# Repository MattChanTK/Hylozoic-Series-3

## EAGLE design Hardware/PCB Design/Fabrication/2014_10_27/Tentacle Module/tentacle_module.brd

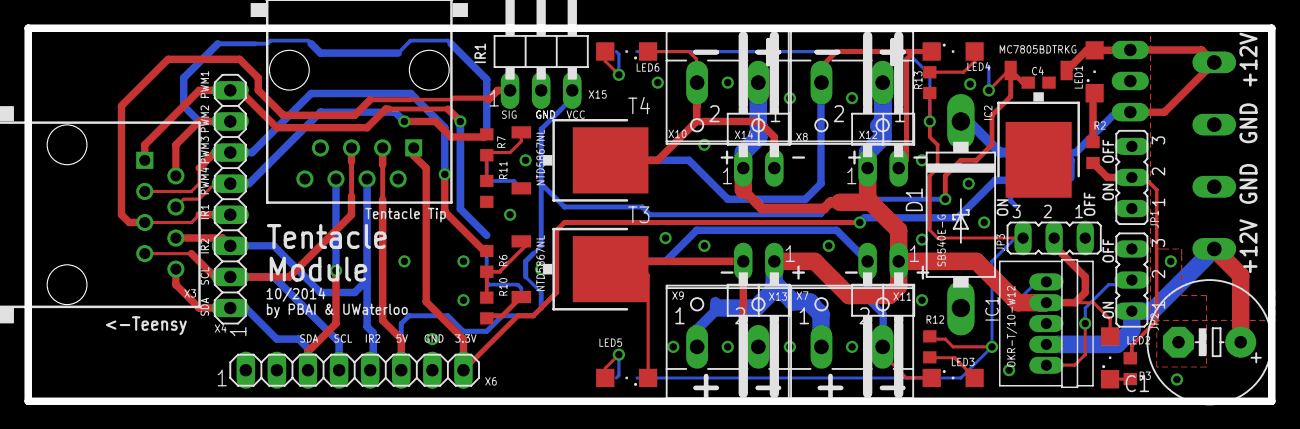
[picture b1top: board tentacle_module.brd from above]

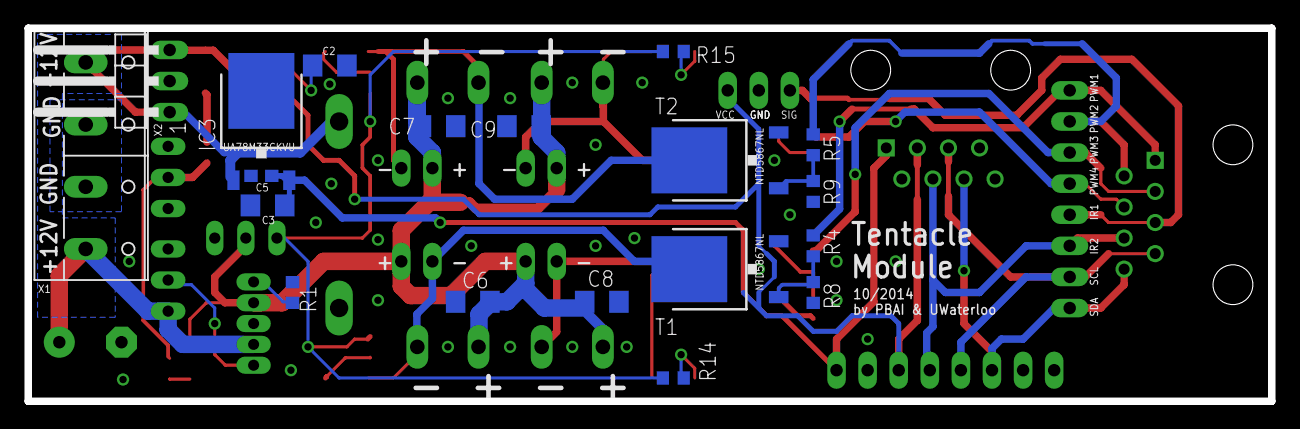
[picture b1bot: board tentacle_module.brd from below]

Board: 2 copper layers, 101.6 x 30.5 mm, 56 parts (19 on the bottom side), 31 nets.

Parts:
C1: 470uF; E5-10,5
C2, C3, C6, C7, C8, C9: 10uF; C1206
C4, C5: 100nF; C0603
D1: SB540E-G; DO201T15
IC1: OKR-T/10-W12; OKR-C90
IC2: MC7805BDTRKG; DPACK_3
IC3: UA78M33CKVU; DPACK
JP1, JP2, JP3: JP2
LED1, LED2, LED3, LED4, LED5, LED6: SML1206
R1: 267; R0603
R2, R3, R12, R13, R14, R15: 470; R0603
R4, R5, R6, R7: 1K; R0603
R8, R9, R10, R11: 4.7K; R0603
T1, T2, T3, T4: NTD5867NL; DPACK
X1: W237-4P
X2, X15: 1X03/90
X3, X5: RJ45-8X; RJ45-NO-SHIELD
X4, X6: 1X08
X7, X8, X9, X10: W237-102
X11, X12, X13, X14: 1X02/90

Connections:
5V_ENABLE: IC1.ON/OFF, JP2.2
+3.3V: C3.1, C5.1, IC3.3, X5.1, X6.8
+5V: C2.1, C4.1, IC2.3, X5.3, X6.6, X15.3
+5V_HI-PWR: C6.1, C7.1, C8.1, C9.1, IC1.VOUT, JP3.2, LED2.A, X7.1, X8.1, X9.1, X10.1, X11.1, X12.1, X13.1, X14.1
+12V: C1.+, D1.C, IC1.VIN, IC2.1, IC3.1, JP2.1, LED1.A, X1.1, X1.4, X2.1, X2.3
GND: C1.-, C2.2, C3.2, C4.2, C5.2, C6.2, C7.2, C8.2, C9.2, D1.A, IC1.GND, IC2.4, IC3.2, JP1.1, JP2.3, R1.1, R8.1, R9.1, R10.1, R11.1, T1.3, T2.3, T3.3, T4.3, X1.2, X1.3, X2.2, X5.2, X6.7, X15.2
IR1: X3.5, X4.4, X15.1
IR2: X3.6, X4.3, X5.4, X6.5
unnamed: R5.2, R9.2, T2.1
unnamed: R6.2, R10.2, T3.1
unnamed: R7.2, R11.2, T4.1
unnamed: R4.2, R8.2, T1.1
unnamed: LED3.A, R12.1
unnamed: IC1.TRIM, R1.2
unnamed: LED2.C, R3.2
unnamed: LED1.C, R2.2
unnamed: LED4.A, R13.1
unnamed: LED5.A, R14.1
unnamed: LED6.A, R15.1
PWM1: R4.1, X3.1, X4.8
PWM2: R5.1, X3.2, X4.7
PWM3: R6.1, X3.3, X4.6
PWM4: R7.1, X3.4, X4.5
PWR_LED_GND: JP1.2, R2.1, R3.1
SCL: X3.7, X4.2, X5.5, X6.4
SDA: X3.8, X4.1, X5.6, X6.3
SMA1_OUT-: LED3.C, T1.2, X7.2, X11.2
SMA2_OUT-: LED4.C, T2.2, X8.2, X12.2
SMA3_OUT-: LED5.C, T3.2, X9.2, X13.2
SMA4_OUT-: LED6.C, T4.2, X10.2, X14.2
TEST_LED_V+: JP3.3, R12.2, R13.2, R14.2, R15.2

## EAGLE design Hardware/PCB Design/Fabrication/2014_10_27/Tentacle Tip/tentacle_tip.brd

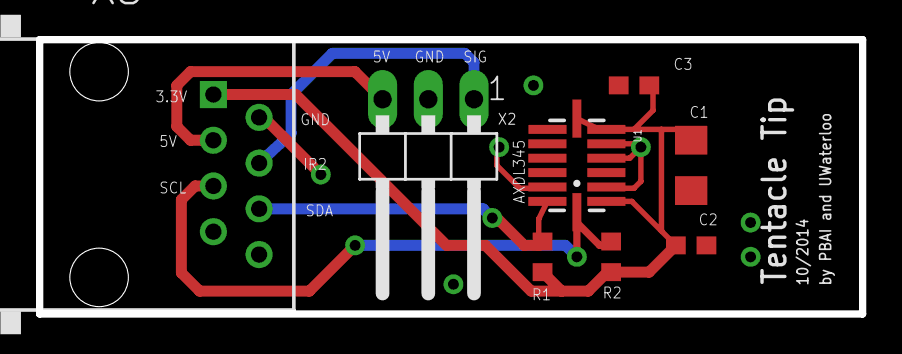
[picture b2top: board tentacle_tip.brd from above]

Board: 2 copper layers, 45.7 x 15.2 mm, 8 parts (0 on the bottom side), 6 nets.

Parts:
C1: 10uF; C1206
C2, C3: 0.1uF; C0603
R1, R2: 2.2k; R0603
U1: ADXL345; LGA14_LONG
X2: 1X03/90
X3: RJ45-8X; RJ45-NO-SHIELD

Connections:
+3.3V: C1.1, C2.1, C3.1, R1.2, R2.2, U1.1, U1.6, U1.7, X3.1
+5V: X2.3, X3.3
GND: C1.2, C2.2, C3.2, U1.2, U1.4, U1.5, U1.12, X2.2, X3.2
IR2: X2.1, X3.4
SCL: R2.1, U1.14, X3.5
SDA: R1.1, U1.13, X3.6

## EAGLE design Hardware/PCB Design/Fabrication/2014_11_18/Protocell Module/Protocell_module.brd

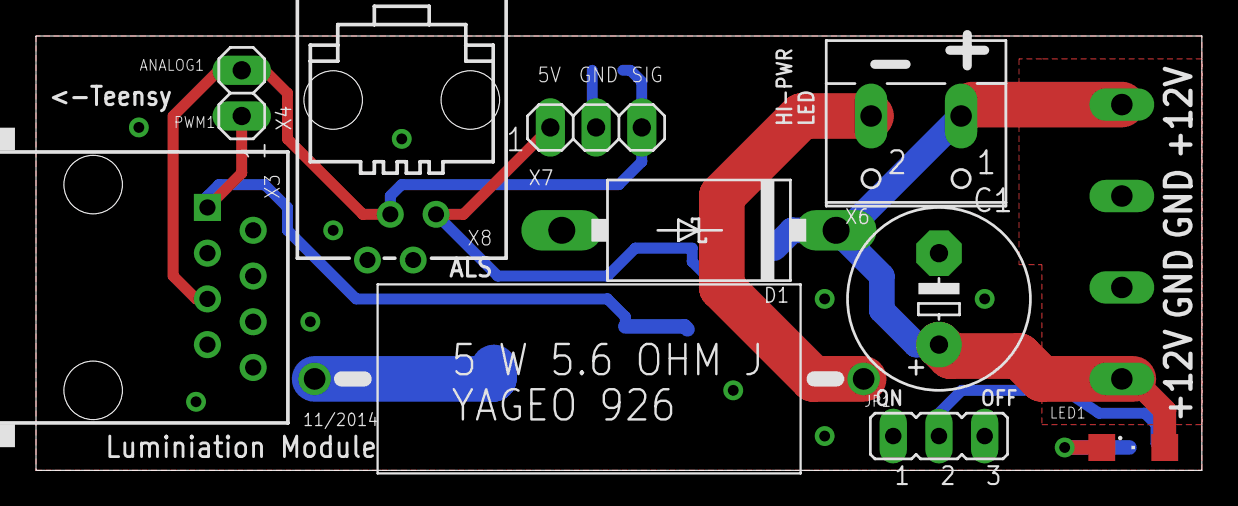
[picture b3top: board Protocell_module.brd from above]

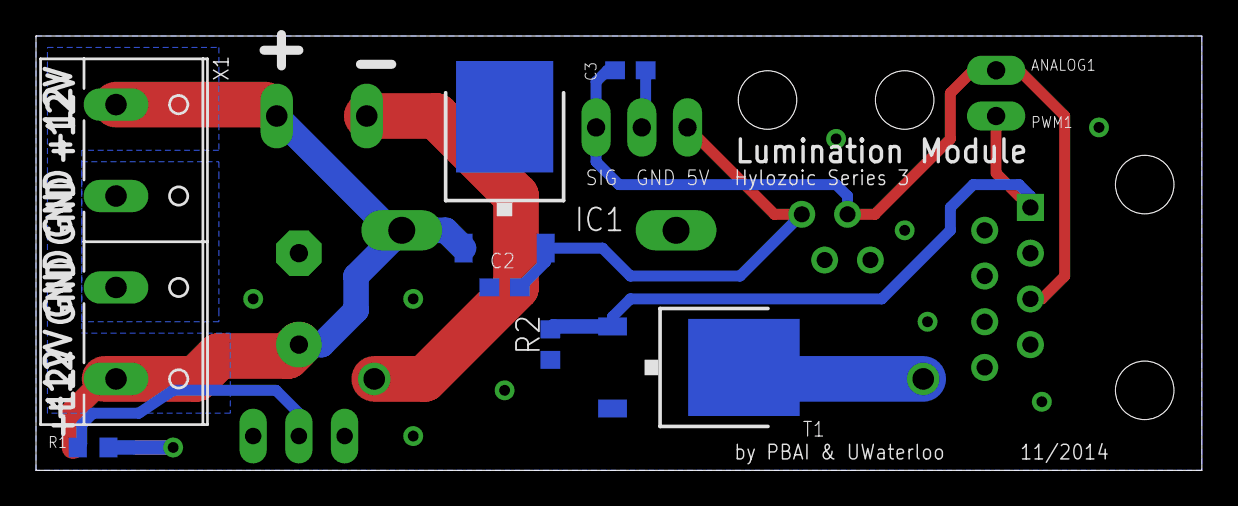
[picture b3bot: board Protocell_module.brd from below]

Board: 2 copper layers, 64.8 x 24.1 mm, 17 parts (7 on the bottom side), 9 nets.

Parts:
C1: 470uF; E5-10,5
C2, C3: 1uF; C0603
D1: SB540E-G; DO201T15
IC1: MC7805BDTRKG; DPACK_3
JP1: JP2
LED1: SML1206
R1: 470; R0603
R2: 4.7k; R0603
R3: 5.6; YAGEO_SQP500JB
T1: DPACK
X1: W237-4P
X3: RJ45-8X; RJ45-NO-SHIELD
X4: 1X02
X6: W237-102
X7: 1X03
X8: 558872-1

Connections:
+5V: C2.1, IC1.3, X7.1, X8.1
+12V: C1.+, D1.C, IC1.1, LED1.A, X1.1, X1.4, X6.1
ANALOG1: C3.1, X3.5, X4.2, X7.3, X8.3
GND: C1.-, C2.2, C3.2, D1.A, IC1.4, JP1.1, R2.1, T1.3, X1.2, X1.3, X7.2, X8.2
unnamed: R3.1, T1.2
unnamed: R3.2, X6.2
unnamed: LED1.C, R1.2
PWM1: R2.2, T1.1, X3.1, X4.1
PWR_LED_GND: JP1.2, R1.1

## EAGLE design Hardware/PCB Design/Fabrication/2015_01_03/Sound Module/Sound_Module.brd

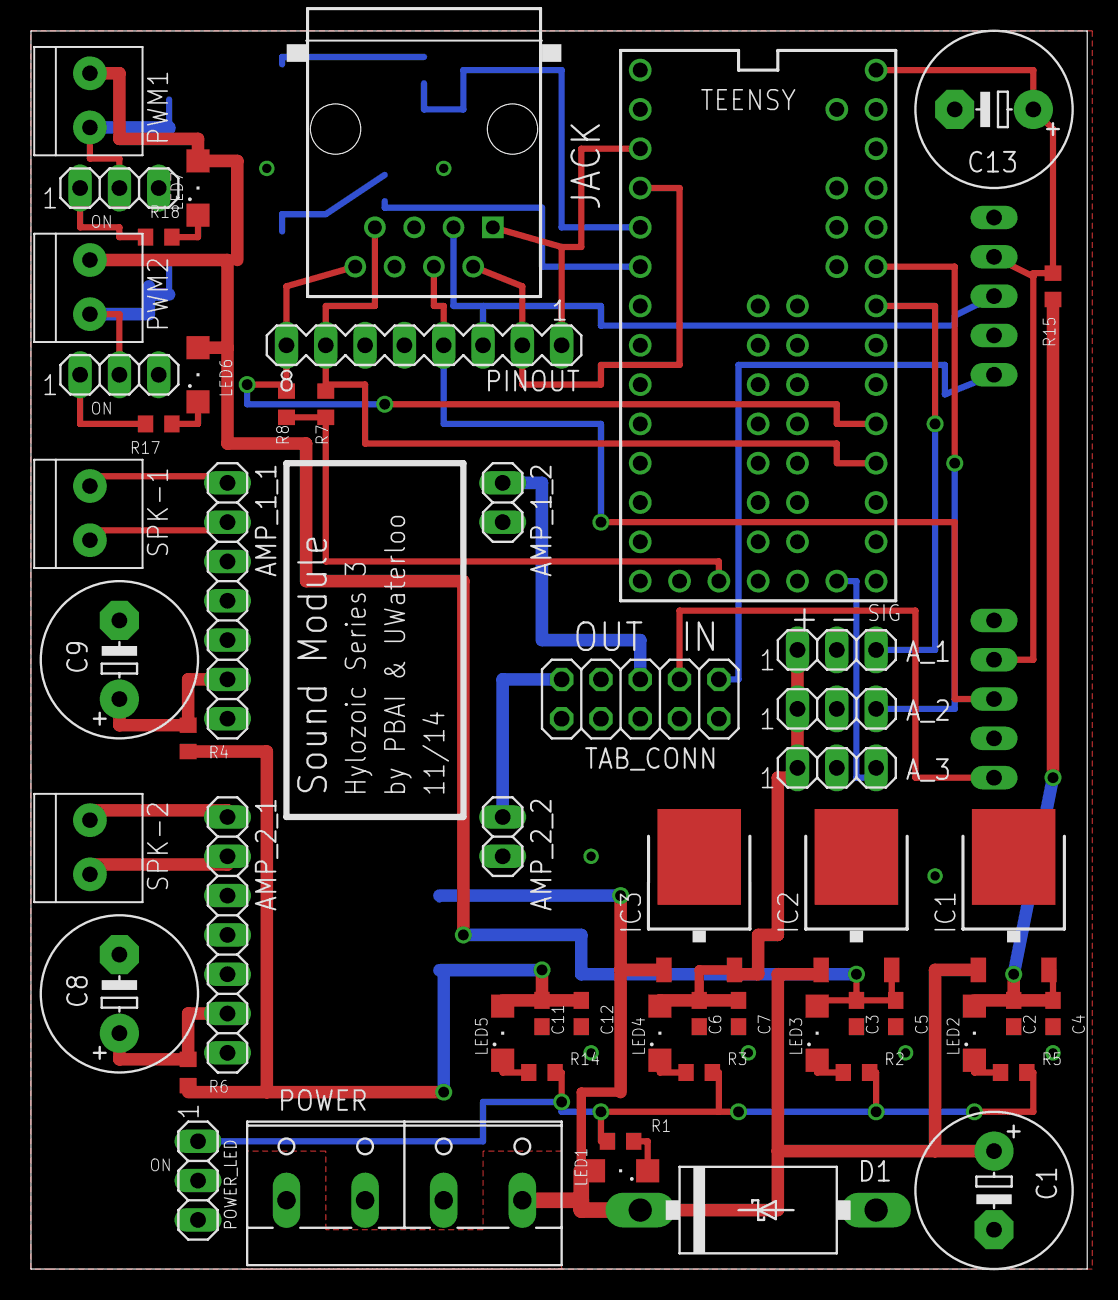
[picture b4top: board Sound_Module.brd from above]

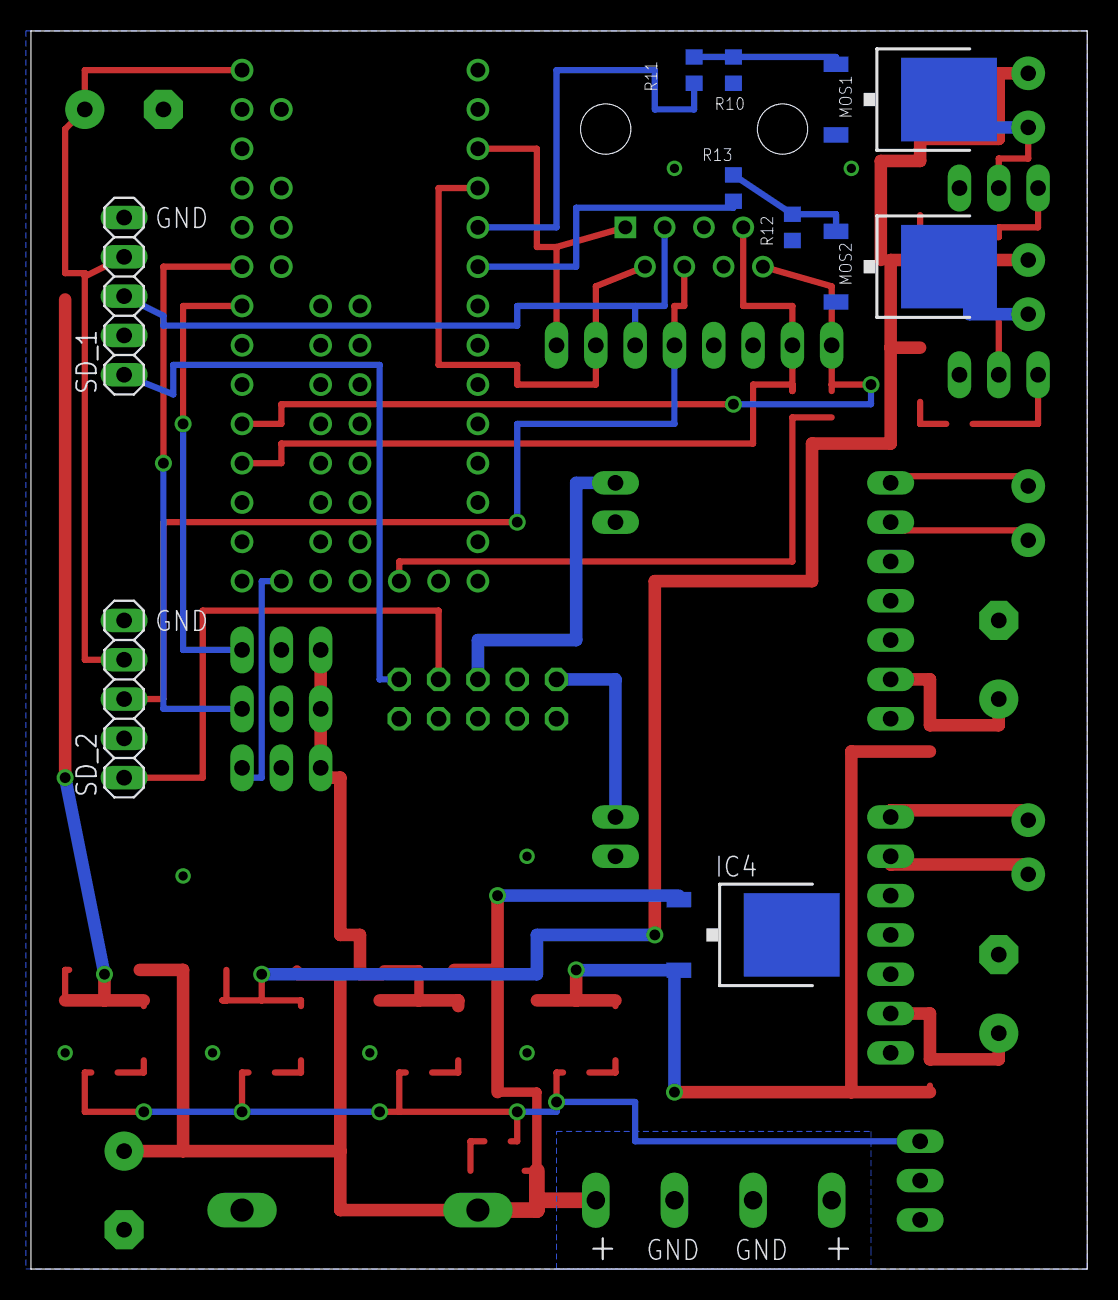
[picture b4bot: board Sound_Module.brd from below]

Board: 2 copper layers, 68.2 x 80.0 mm, 63 parts (9 on the bottom side), 43 nets.

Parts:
AMP_1_1, AMP_2_1: 1X07
AMP_1_2, AMP_2_2: 1X02
A_1, A_2, A_3: 1X03
C1: 2000uF; E5-10,5
C2, C3, C6, C11: 1uF; C0603
C4, C5, C7, C12: 100nF; C0603
C8, C9, C13: 470uF; E5-10,5
D1: SB540E-G; DO201T15
IC1, IC2, IC3, IC4: DPACK_3
JACK: RJ45-6L-B; RJ45-NO-SHIELD
LED1, LED2, LED3, LED4, LED5, LED6, LED7: SML1206
MOS1, MOS2: DPACK
PINOUT: MA08-1
POWER: W237-4P
POWER_LED: 1X03
PWM1, PWM2: 1X2-3.5MM
R1, R2, R3, R5, R14, R17, R18: 470; R0603
R4, R6, R15: 10; R0603
R7, R8: 2.2k; R0603
R10, R12: 4.7K; R0603
R11, R13: 1K; R0603
SD_1, SD_2: 1X05
SPK-1, SPK-2: 1X2-3.5MM
TAB_CONN: 2X05
TEENSY: AUDIO BOARD; TEENSY_3.1_ALLPINS
X2, X3: 1X03

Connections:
3.3V: R7.2, R8.2, TEENSY.3.3V, TEENSY.3.3V1, TEENSY.3.3V2
5VFILT: C13.+, R15.1, SD_1.4, SD_2.4, TEENSY.VIN
+5V_1: C2.1, C4.1, IC1.3, LED2.A, R15.2
+5V_2: C3.1, C5.1, IC2.3, LED3.A, LED6.A, LED7.A, PWM1.2, PWM2.2
+5V_3: A_1.1, A_2.1, A_3.1, C6.1, C7.1, IC3.3, LED4.A
+5V_4: C11.1, C12.1, IC4.3, LED5.A, R4.2, R6.2
+12V: C1.+, D1.C, IC1.1, IC2.1, IC3.1, IC4.1, LED1.A, POWER.1, POWER.4
AMP_1_VIN: AMP_1_1.6, C9.+, R4.1
AMP_2_VIN: AMP_2_1.6, C8.+, R6.1
DPEAK_1: JACK.3, PINOUT.3, SD_1.3
DPEAK_2: JACK.4, PINOUT.4, SD_2.3
DTRIG_1: JACK.1, PINOUT.1, TEENSY.1
DTRIG_2: JACK.2, PINOUT.2, TEENSY.2
FPWM_1_1: R11.2, TEENSY.3
FPWM_1_2: R13.2, TEENSY.4
GND: AMP_1_1.5, AMP_1_2.2, AMP_2_1.5, AMP_2_2.2, A_1.2, A_2.2, A_3.2, C1.-, C2.2, C3.2, C4.2, C5.2, C6.2, C7.2, C8.-, C9.-, C11.2, C12.2, C13.-, D1.A, IC1.4, IC2.4, IC3.4, IC4.4, MOS1.3, MOS2.3, POWER.2, POWER.3, POWER_LED.2, R10.1, R12.1, SD_1.5, SD_2.5, TAB_CONN.2, TAB_CONN.4, TAB_CONN.7, TEENSY.GND, TEENSY.GND1, TEENSY.GND2
IN_1+: AMP_1_2.1, TAB_CONN.5
IN_2+: AMP_2_2.1, TAB_CONN.9
LED_JUMP_POW: POWER_LED.1, R1.1, R2.1, R3.1, R5.1, R14.1
MIC_1: SD_1.1, TAB_CONN.1
MIC_2: SD_2.1, TAB_CONN.3
unnamed: MOS2.1, R12.2, R13.1
unnamed: LED3.C, R2.2
unnamed: LED4.C, R3.2
unnamed: MOS1.1, R10.2, R11.1
unnamed: MOS1.2, PWM1.1, X2.2
unnamed: LED6.C, R17.2
unnamed: MOS2.2, PWM2.1, X3.2
unnamed: LED5.C, R14.2
unnamed: LED7.C, R18.2
unnamed: LED1.C, R1.2
unnamed: R18.1, X2.1
unnamed: R17.1, X3.1
unnamed: LED2.C, R5.2
SCL: JACK.7, PINOUT.7, R7.1, TEENSY.16/A2
SDA: JACK.8, PINOUT.8, R8.1, TEENSY.17/A3
SIG_1: A_1.3, TEENSY.20/A6
SIG_2: A_2.3, TEENSY.21/A7
SIG_3: A_3.3, TEENSY.A14
SPK_1+: AMP_1_1.1, SPK-1.2
SPK_1-: AMP_1_1.2, SPK-1.1
SPK_2+: AMP_2_1.1, SPK-2.2
SPK_2-: AMP_2_1.2, SPK-2.1

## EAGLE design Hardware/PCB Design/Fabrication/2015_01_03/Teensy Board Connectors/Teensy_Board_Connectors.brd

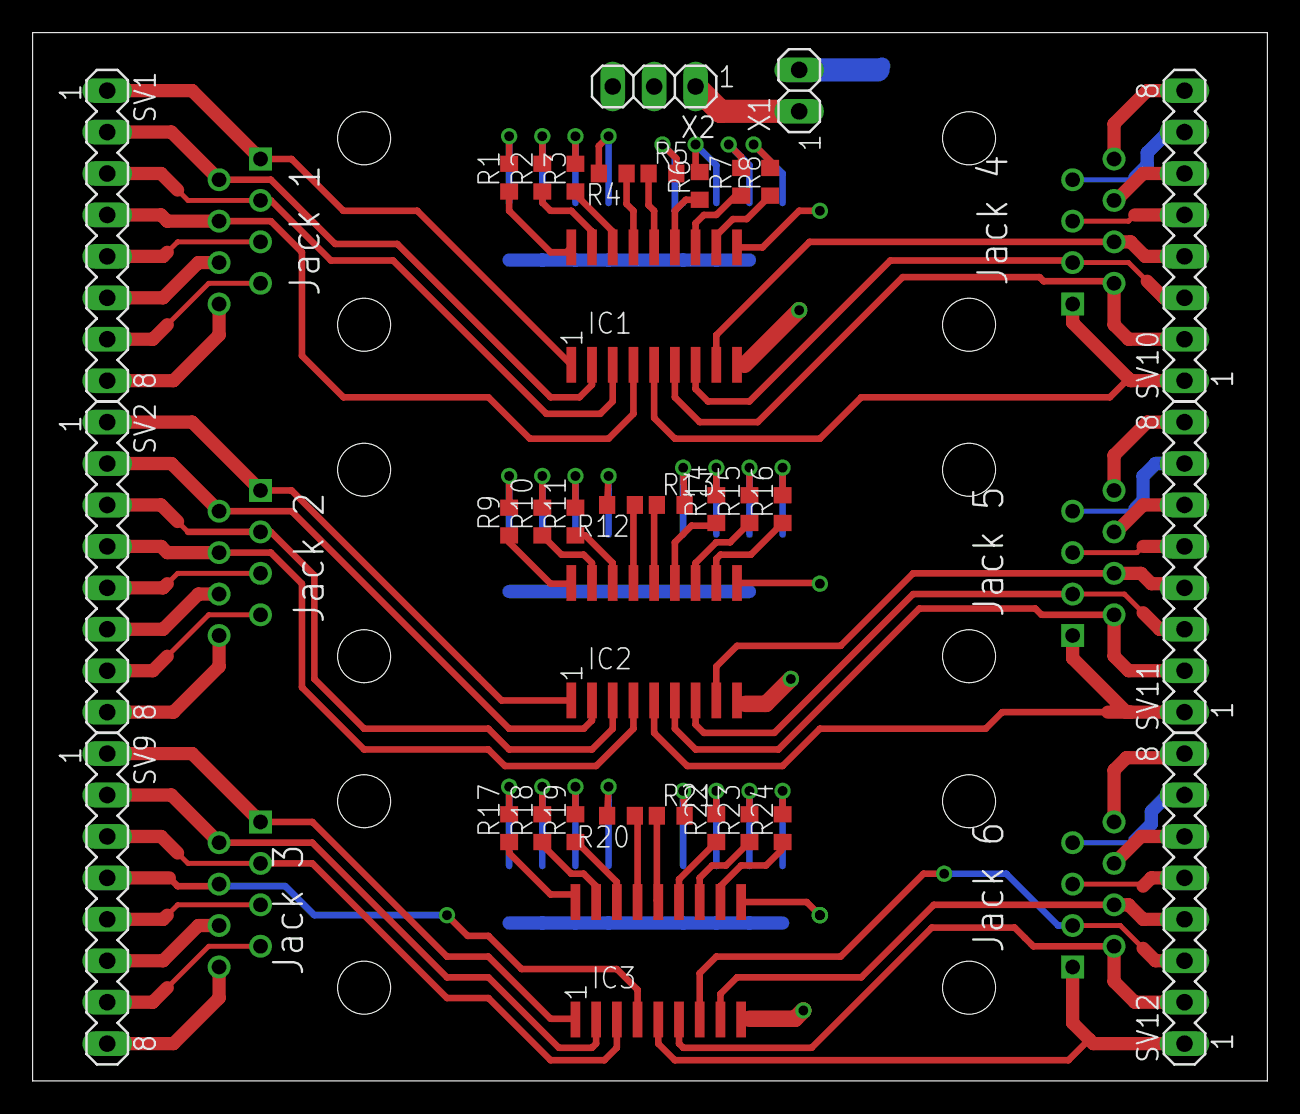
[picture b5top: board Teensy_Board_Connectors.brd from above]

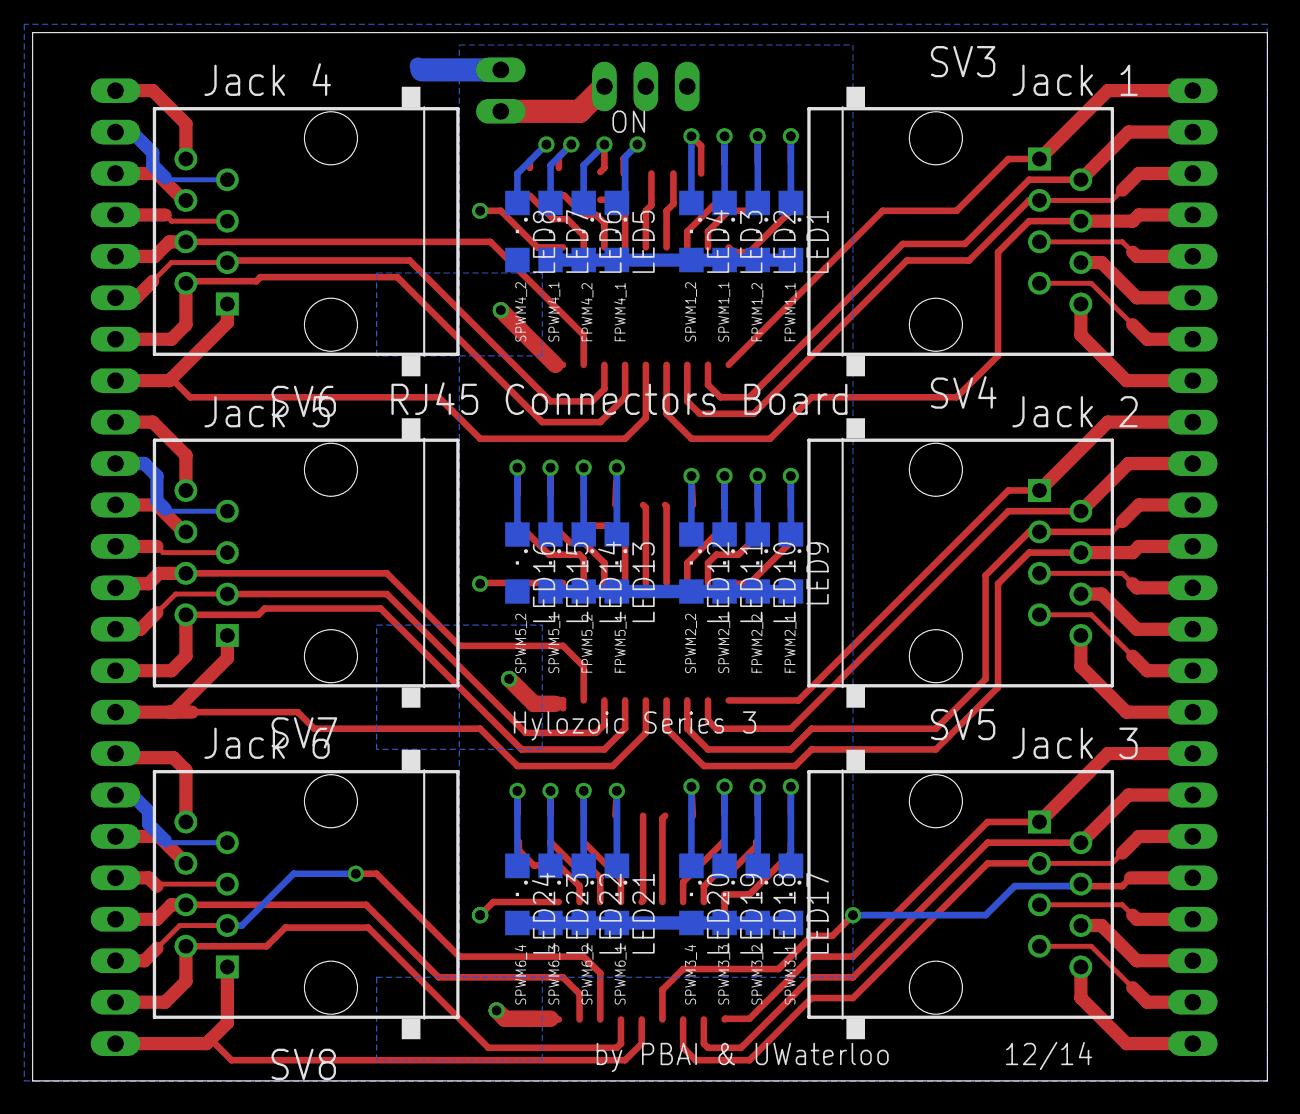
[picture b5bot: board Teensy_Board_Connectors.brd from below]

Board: 2 copper layers, 75.7 x 64.3 mm, 65 parts (30 on the bottom side), 99 nets.

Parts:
IC1, IC2, IC3: SOP18
LED1, LED2, LED3, LED4, LED5, LED6, LED7, LED8, LED9, LED10, LED11, LED12, LED13, LED14, LED15, LED16, LED17, LED18, LED19, LED20, LED21, LED22, LED23, LED24: SML1206
R1, R2, R3, R4, R5, R6, R7, R8, R9, R10, R11, R12, R13, R14, R15, R16, R17, R18, R19, R20, R21, R22, R23, R24: 470; R0603
SV1, SV2, SV9, SV10, SV11, SV12: MA08-1
SV3, SV4, SV5, SV6, SV7, SV8: RJ45-8X; RJ45-NO-SHIELD
X1: 1X02
X2: 1X03

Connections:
+5V: IC1.10, IC2.10, IC3.10, LED1.A, LED2.A, LED3.A, LED4.A, LED5.A, LED6.A, LED7.A, LED8.A, LED9.A, LED10.A, LED11.A, LED12.A, LED13.A, LED14.A, LED15.A, LED16.A, LED17.A, LED18.A, LED19.A, LED20.A, LED21.A, LED22.A, LED23.A, LED24.A, X2.2
+5VJUMP: X1.1, X2.1
A0: SV8.5, SV12.5
A1: SV8.6, SV12.6
A2: SV7.5, SV11.5
A3: SV7.6, SV11.6
A8: SV6.5, SV10.5
A9: SV6.6, SV10.6
A11: SV1.5, SV3.5
A12: SV2.5, SV4.5
A13: SV1.6, SV3.6
A15: SV2.6, SV4.6
A16: SV5.5, SV9.5
A17: SV5.6, SV9.6
FPWM_1_1: IC1.1, SV1.1, SV3.1
FPWM_1_2: IC1.2, SV1.2, SV3.2
FPWM_2_1: IC2.1, SV2.1, SV4.1
FPWM_2_2: IC2.2, SV2.2, SV4.2
FPWM_4_1: IC1.5, SV6.1, SV10.1
FPWM_4_2: IC1.6, SV6.2, SV10.2
FPWM_5_1: IC2.5, SV7.1, SV11.1
FPWM_5_2: IC2.6, SV7.2, SV11.2
GND: IC1.9, IC2.9, IC3.9, X1.2
MUL_SCL_1: SV1.7, SV3.7
MUL_SCL_2: SV2.7, SV4.7
MUL_SCL_3: SV5.7, SV9.7
MUL_SCL_4: SV6.7, SV10.7
MUL_SCL_5: SV7.7, SV11.7
MUL_SCL_6: SV8.7, SV12.7
MUL_SDA_1: SV1.8, SV3.8
MUL_SDA_2: SV2.8, SV4.8
MUL_SDA_3: SV5.8, SV9.8
MUL_SDA_4: SV6.8, SV10.8
MUL_SDA_5: SV7.8, SV11.8
MUL_SDA_6: SV8.8, SV12.8
unnamed: IC1.18, R1.1
unnamed: LED1.C, R1.2
unnamed: IC1.17, R2.1
unnamed: IC1.16, R3.1
unnamed: IC1.15, R4.1
unnamed: IC1.14, R5.1
unnamed: IC1.13, R6.1
unnamed: IC1.12, R7.1
unnamed: IC1.11, R8.1
unnamed: LED2.C, R2.2
unnamed: LED3.C, R3.2
unnamed: LED4.C, R4.2
unnamed: LED5.C, R5.2
unnamed: LED6.C, R6.2
unnamed: LED7.C, R7.2
unnamed: LED8.C, R8.2
unnamed: IC2.18, R9.1
unnamed: LED9.C, R9.2
unnamed: IC2.17, R10.1
unnamed: IC2.16, R11.1
unnamed: IC2.15, R12.1
unnamed: IC2.14, R13.1
unnamed: IC2.13, R14.1
unnamed: IC2.12, R15.1
unnamed: IC2.11, R16.1
unnamed: LED10.C, R10.2
unnamed: LED11.C, R11.2
unnamed: LED12.C, R12.2
unnamed: LED13.C, R13.2
unnamed: LED14.C, R14.2
unnamed: LED15.C, R15.2
unnamed: LED16.C, R16.2
unnamed: IC3.18, R17.1
unnamed: LED17.C, R17.2
unnamed: IC3.17, R18.1
unnamed: IC3.16, R19.1
unnamed: IC3.15, R20.1
unnamed: IC3.14, R21.1
unnamed: IC3.13, R22.1
unnamed: IC3.12, R23.1
unnamed: IC3.11, R24.1
unnamed: LED18.C, R18.2
unnamed: LED19.C, R19.2
unnamed: LED20.C, R20.2
unnamed: LED21.C, R21.2
unnamed: LED22.C, R22.2
unnamed: LED23.C, R23.2
unnamed: LED24.C, R24.2
SPWM_1_1: IC1.3, SV1.3, SV3.3
SPWM_1_2: IC1.4, SV1.4, SV3.4
SPWM_2_1: IC2.3, SV2.3, SV4.3
SPWM_2_2: IC2.4, SV2.4, SV4.4
SPWM_3_1: IC3.1, SV5.1, SV9.1
SPWM_3_2: IC3.2, SV5.2, SV9.2
SPWM_3_3: IC3.3, SV5.3, SV9.3
SPWM_3_4: IC3.4, SV5.4, SV9.4
SPWM_4_1: IC1.7, SV6.3, SV10.3
SPWM_4_2: IC1.8, SV6.4, SV10.4
SPWM_5_1: IC2.7, SV7.3, SV11.3
SPWM_5_2: IC2.8, SV7.4, SV11.4
SPWM_6_1: IC3.5, SV8.1, SV12.1
SPWM_6_2: IC3.6, SV8.2, SV12.2
SPWM_6_3: IC3.7, SV8.3, SV12.3
SPWM_6_4: IC3.8, SV8.4, SV12.4

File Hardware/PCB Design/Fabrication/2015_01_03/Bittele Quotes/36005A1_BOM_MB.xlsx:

| Tentacle Tip Bill of Materials (BOM)_Bittele Electronics Inc.
Item # | Ref Des | Description | Qty | Manufacturer | Mfg Part # | Package | Type | Your Instructions |  | Total Required for 10 Boards | Packed
1 | LED1, LED2, LED3, LED4, LED5, LED6, LED7, LED8, LED9, LED10, LED11, LED12, LED1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 | LED 3.2X1.6MM 568NM GRN CLR SMD | 24 | Kingbright | APTR3216SGC | 1206 | SMD |  |  | 240 | 0
2 | SV1, SV2, SV9, SV10, SV11, SV12 | CONN HEADER .100" SNGL STR 8POS | 6 | Sullins Connector Solutions | PREC008SAAN-RC | 0.100" (2.54mm) | thru-hole |  |  | 60 | 0
3 | X1 | CONN HEADER .100" SNGL STR 2POS | 1 | Sullins Connector Solutions | PREC002SAAN-RC | 0.100" (2.54mm) | thru-hole |  |  | 10 | 0
4 | X2 | CONN HEADER .100" SNGL STR 3POS | 1 | Sullins Connector Solutions | PREC003SAAN-RC | 0.100" (2.54mm) | thru-hole |  |  | 10 | 0
5 | IC1, IC2, IC3 | TRANS 8NPN DARL 50V 0.5A 18SOL | 3 | Toshiba Semiconductor and Storage | ULN2803AFWG,C,EL | 18-SOIC | SMD |  |  | 30 | 0
6 | R1, R2, R3, R4, R5, R6, R7, R8, R9, R10, R11, R12, R13, R14, R15, R16, R17, R18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 | RES 470 OHM 1/4W 5% 0603 SMD | 24 | Rohm Semiconductor | RHM470DCT-ND | 0603 | SMD |  |  | 240 | 0
7 | SV3, SV4, SV5, SV6, SV7, SV8 | CONN MOD JACK 8P8C | 6 | FCI | 54602-908LF |  | thru-hole |  |  | 60 | 63

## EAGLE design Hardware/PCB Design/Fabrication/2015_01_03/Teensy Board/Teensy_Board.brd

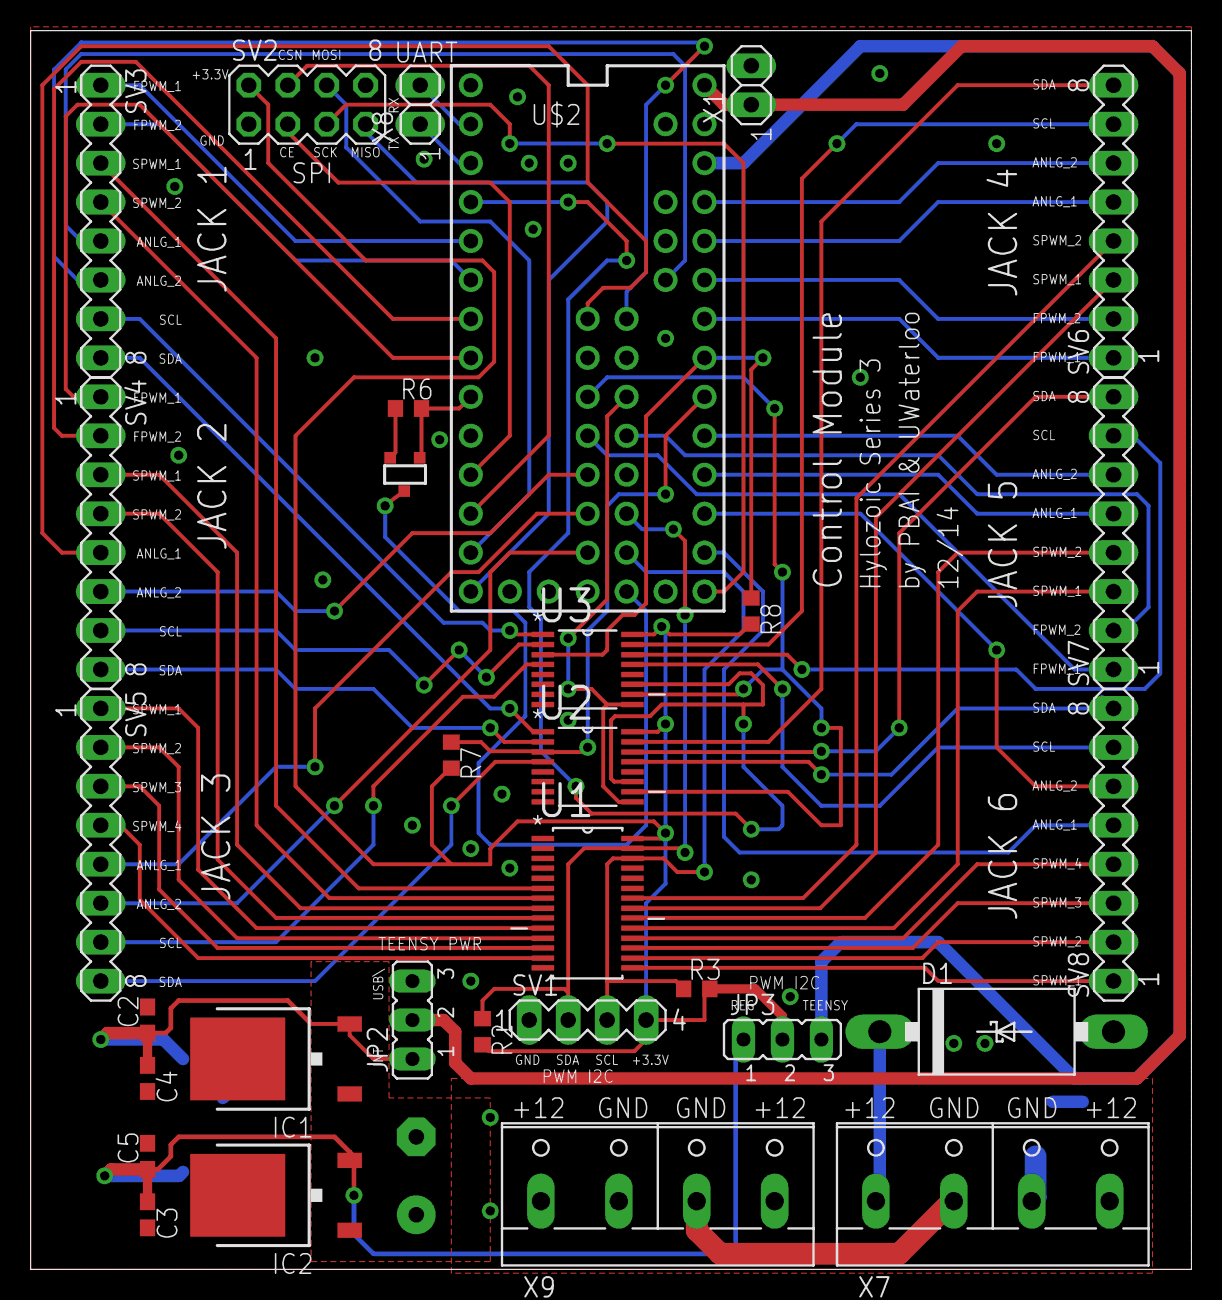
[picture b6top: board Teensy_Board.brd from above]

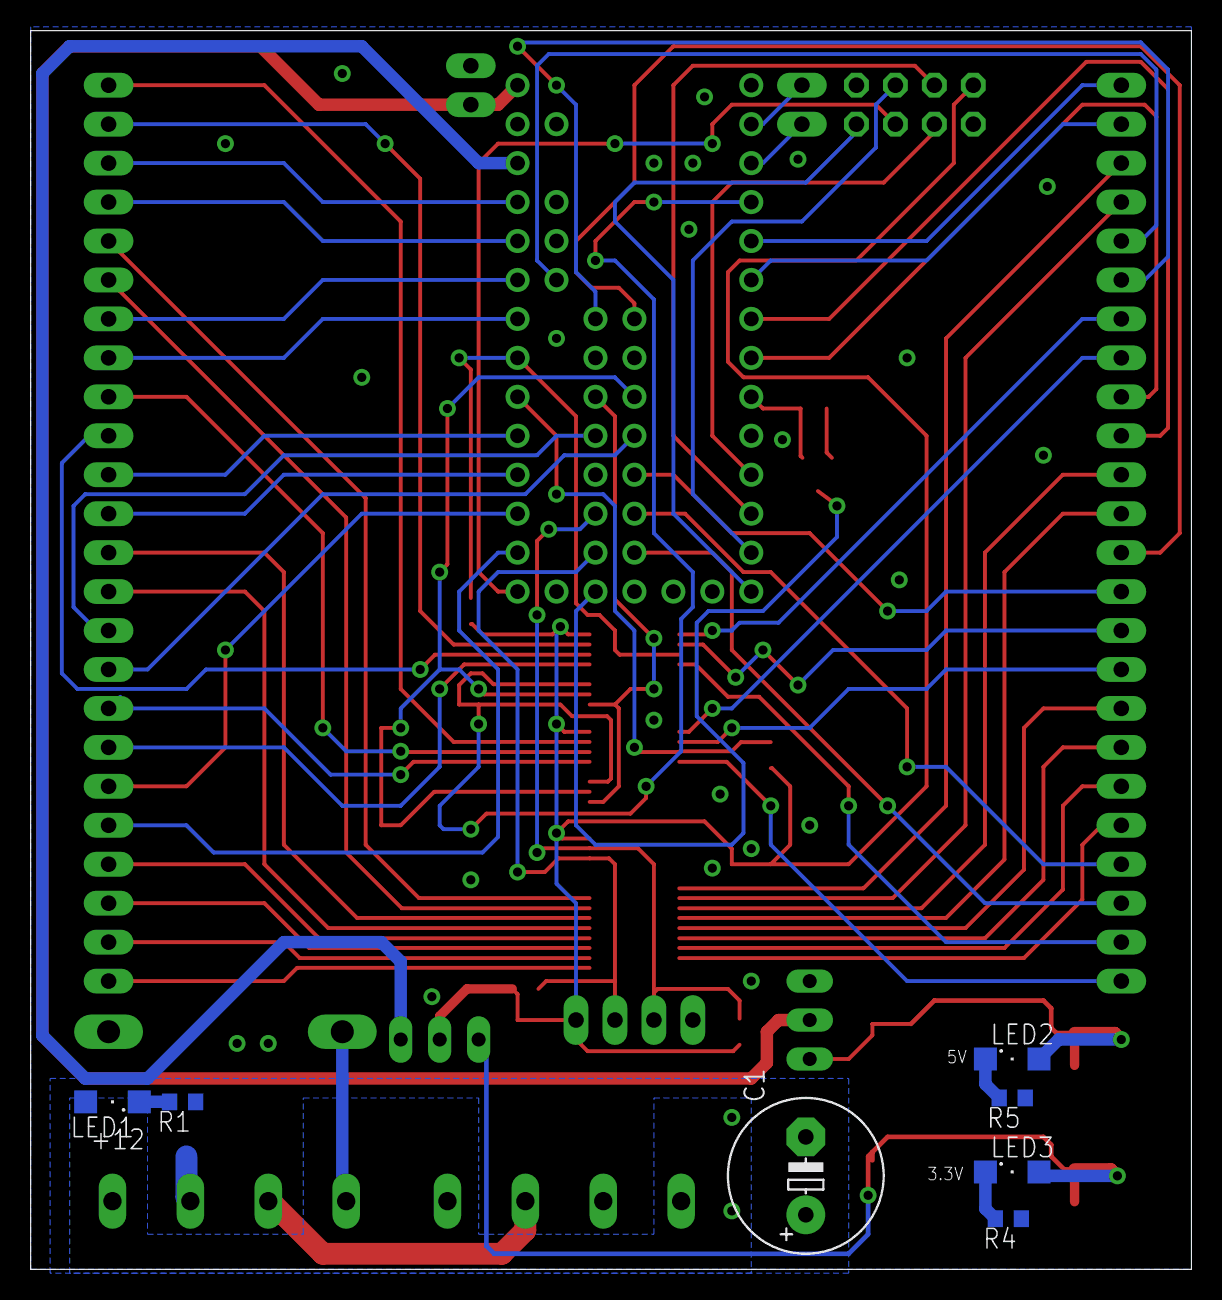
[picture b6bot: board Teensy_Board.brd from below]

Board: 2 copper layers, 75.7 x 80.8 mm, 38 parts (7 on the bottom side), 74 nets.

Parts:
C1: 470uF; E5-10,5
C2, C3: 1uF; C0603
C4, C5: 100nF; C0603
D1: SB540E-G; DO201T15
IC1: MC7805BDTRKG; DPACK_3
IC2: UA78M33CKVU; DPACK
JP2, JP3: JP2
LED1, LED2, LED3: SML1206
Q1: PROGRAM_FET; SOT-23
R1, R4, R5: 470; R0603
R2, R3, R6: 4k7; R0603
R7, R8: 2.2k; R0603
SV1: PWM_I2C; MA04-1
SV2: SPI; MA04-2
SV3, SV4, SV5, SV6, SV7, SV8: MA08-1
U1: PCA9685PW; SOP65P640X110-28N
U2, U3: 74HC4051PW,118; SOP65P640X110-16N
U$2: TEENSY_3.1_ALL_PINS_AND_PADS; TEENSY_3.1_ALLPINS
X1: 1X02
X7, X9: W237-4P
X8: UART; 1X02

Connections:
3V3INT: JP3.2, R2.2, R3.2, R7.2, R8.2, SV1.4, SV2.2, U1.28, U2.16, U3.16
+3V3: C3.1, C5.1, IC2.3, JP3.1, LED3.A
+5V: C2.1, C4.1, IC1.3, JP2.1, LED2.A
+12V: C1.+, D1.C, IC1.1, IC2.1, LED1.A, X7.1, X7.4, X9.1, X9.4
A0: SV8.5, U$2.14/A0
A1: SV8.6, U$2.15/A1
A2: SV7.5, U$2.16/A2
A3: SV7.6, U$2.17/A3
A8: SV6.5, U$2.22/A8
A9: SV6.6, U$2.23/A9
A11: SV3.5, U$2.A11
A12: SV4.5, U$2.A12
A13: SV3.6, U$2.A13
A15: SV4.6, U$2.26
A16: SV5.5, U$2.27
A17: SV5.6, U$2.28
CE: SV2.3, U$2.9
CSN: SV2.4, U$2.10
FPWM_1_1: SV3.1, U$2.3
FPWM_1_2: SV3.2, U$2.4
FPWM_2_1: SV4.1, U$2.6
FPWM_2_2: SV4.2, U$2.5
FPWM_4_1: SV6.1, U$2.20/A6
FPWM_4_2: SV6.2, U$2.21/A7
FPWM_5_1: SV7.1, U$2.25
FPWM_5_2: SV7.2, U$2.32
GND: C1.-, C2.2, C3.2, C4.2, C5.2, D1.A, IC1.4, IC2.2, Q1.2, R1.1, R4.1, R5.1, R6.1, SV1.1, SV2.1, U1.1, U1.2, U1.3, U1.4, U1.5, U1.14, U1.23, U1.24, U1.25, U2.6, U2.7, U2.8, U3.6, U3.7, U3.8, U$2.GND, U$2.GND1, U$2.GND2, X1.2, X7.2, X7.3, X9.2, X9.3
MISO: SV2.7, U$2.12
MOSI: SV2.6, U$2.11
MUL_ADR_0: U2.11, U3.11, U$2.2
MUL_ADR_1: U2.10, U3.10, U$2.24
MUL_ADR_2: U2.9, U3.9, U$2.33
MUL_SCL: R8.1, U3.3, U$2.19/A5
MUL_SCL_1: SV3.7, U3.1
MUL_SCL_2: SV4.7, U3.2
MUL_SCL_3: SV5.7, U3.4
MUL_SCL_4: SV6.7, U3.15
MUL_SCL_5: SV7.7, U3.14
MUL_SCL_6: SV8.7, U3.13
MUL_SDA: R7.1, U2.3, U$2.18/A4
MUL_SDA_1: SV3.8, U2.1
MUL_SDA_2: SV4.8, U2.2
MUL_SDA_3: SV5.8, U2.4
MUL_SDA_4: SV6.8, U2.15
MUL_SDA_5: SV7.8, U2.14
MUL_SDA_6: SV8.8, U2.13
unnamed: LED1.C, R1.2
unnamed: LED3.C, R4.2
unnamed: LED2.C, R5.2
PGM: Q1.3, U$2.PGM
PGM_DO: Q1.1, R6.2, U$2.7
RX1: U$2.0, X8.2
SCK: SV2.5, U$2.13
SCL_PWM: R3.1, SV1.3, U1.26, U$2.29
SDA_PWM: R2.1, SV1.2, U1.27, U$2.30
SPWM_1_1: SV3.3, U1.6
SPWM_1_2: SV3.4, U1.7
SPWM_2_1: SV4.3, U1.8
SPWM_2_2: SV4.4, U1.9
SPWM_3_1: SV5.1, U1.10
SPWM_3_2: SV5.2, U1.11
SPWM_3_3: SV5.3, U1.12
SPWM_3_4: SV5.4, U1.13
SPWM_4_1: SV6.3, U1.21
SPWM_4_2: SV6.4, U1.22
SPWM_5_1: SV7.3, U1.19
SPWM_5_2: SV7.4, U1.20
SPWM_6_1: SV8.1, U1.15
SPWM_6_2: SV8.2, U1.16
SPWM_6_3: SV8.3, U1.17
SPWM_6_4: SV8.4, U1.18
TEENSY_3V3: JP3.3, U$2.3.3V, U$2.3.3V1, U$2.3.3V2
TEENSY_VIN: JP2.2, U$2.VIN, X1.1
TX1: U$2.1, X8.1
